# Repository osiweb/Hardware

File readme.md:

## Synopsis

Ohio Scientific was one of the early makers of home computers, from the mid 70's to the mid 80's.  It's user base was small back then, and now a small number of hobbyists still hold some affection for these machines.  OSI hobbyists tend to appreciate the large, sparsely populated boards, which were easy to understand and hack.

This project aims preserve the designs by archiving the boards as quality gerbers, so that almost any OSI system can be reproduced.  Some boards have been scanned and post-processed.  Others have been recreated by hand.  This is a community project and any contributions are welcome.

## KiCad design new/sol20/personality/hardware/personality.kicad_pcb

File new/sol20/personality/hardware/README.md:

# Sol-20 unversal peronality module

## Introduction

This is a "Universal" personality module for the SOL-20.  It's features include:

* Up to 16 ROM images, which can be selected by jumper configuration.

* Supports 27/28C256, 27/28C128, 27/28C64

* Supports remapping ROM, sysem RAM, and video to Fxxx, with a trivial mod to
  the motherboard (and re-assembling ROM images to run at F000). The mod does
  not require cutting any traces, so it's fully reversible and doesn't require
  modifications to other personality modules to be used with the modified
  mainboard, unlike the modification described in the Micro Complex manual.

## Parts

1. U1 - 74LS08

1. U2 - 27C256/28C256/27C128/28C128/27C64/28C64, or compatible parts.

1. RN1 - SIP resistor network with common pin 1. Any 6-, 7-, or 8 resistor
   network in the 3.3K-10K range will be fine, as long as you place it on the
   board with pin 1 in the right spot.

1. RN2 - SIP resistor network with common pin 1. Can use the same part as RN1.
   Any value in the 1K-20K range will work. Minimal current through this
   network. is fine, and you can use any value at all, or even just solder a
   wire across all the pins (negligible current should flow through the
   network).

1. JP1 - 2 x 8 pin 0.1" breakaway header.

## Fxxx mapping modification - no mainboard modification

1. You may want to order a spare DIP 74LS136 chip. This is the quad
   open-collector XOR gate at U22. Not only will this let you preserve the
   original chip with the correct date code; you will have to solder some wires directly
   to the pins of U22, and this might be easier and cleaner on a new chip rather than an
   old chip wiht oxidized leads.

1. Make or buy a 2-wire cable with 2-pin female socket header.  You can buy one premade,
   such as [this one from Sparkfun](https://www.sparkfun.com/products/10372.

1. With the universal personality module inserted, install the cable header on
   the PCB pin header position labeled "Map header". This is on the far right if
   the edge connector is facing you.
   
1. Neatly route the cable from the header to pins 3 and 5 of U22, leaving a bit
   of slack.
   
1. Cut the cable to length, and strip 2mm from the cable ends.

1. Solder the cable wires to pins 3 and 5 of of a 74LS136 chip. If you solder
   the wire with the chip removed from the main board, you can make a clean
   joint without worrying about damaging the socket or splashing solder on the
   main board.

1. Plug the 74LS136 in the U22 socket

1. Plug the female cable connector into the "Map Header" pins Route the cable
   neatly, securing it with small tie wraps where possible.
   
<!-- ## Fxxx mapping modification - No cable (Requires mainboard removal, which is somwhat involved) (NOT RECOMMENDED -- THIS IS NOT TESTED, AND NEEDS TO BE REVIEWED) -->

<!-- 1. Remove the SOL-PC mainboard from the case. -->
<!-- 1. Solder a jumper wire between pin 3 of U22 and pin B2 of J5 (the personality module connector.) -->
<!-- 1. Solder a jumper wire between pin 5 of U22 and pin B3 of J5. -->
<!-- 1. Reinstall the SOL-PC mainboard and reassemble. -->

## To remap the ROM, system RAM, and video to Fxxx (with one of the mods above)

1. First, make sure the selected ROM image is compiled for Fxxx.

1. Place a jumper in the "Map Fxxx" position.

1. To revert to Cxxx, make sure the selected image is compiled for Cxxx and
   remove the "Map Fxxx" jumper.

## Notes

1. For the SEL0-3 lines, a jumper pulls the line LOW, so the 000 block will
   require 3 jumpers. If you want a jumper to indicate a logical 1, then invert
   the ordering of the images in the (E)EPROM. I.E., place the first image at
   111, second at 110, third at 101, etc. Since that can all be handled in a
   script, that's not a bad way to go.

1. For a 'C128, leave Sel3 open. For a 'C64, leave Sel 2 and Sel 3 open.

1. If you use a 28C256 or 27C256, you need to jumper-select the (E)EPROM type.
   For a 27C256, place the jumper at the 27C256 position. For 28C256 place the
   jumper at 28C256 position.  For all other types, leave both jumpers empty.

1. The Resistor network values are not critical at all. The two networks don't
   need to be the same, or even have the same number of pins, as long as there
   are at least 6 resistors, and pin 1 is the common pin.

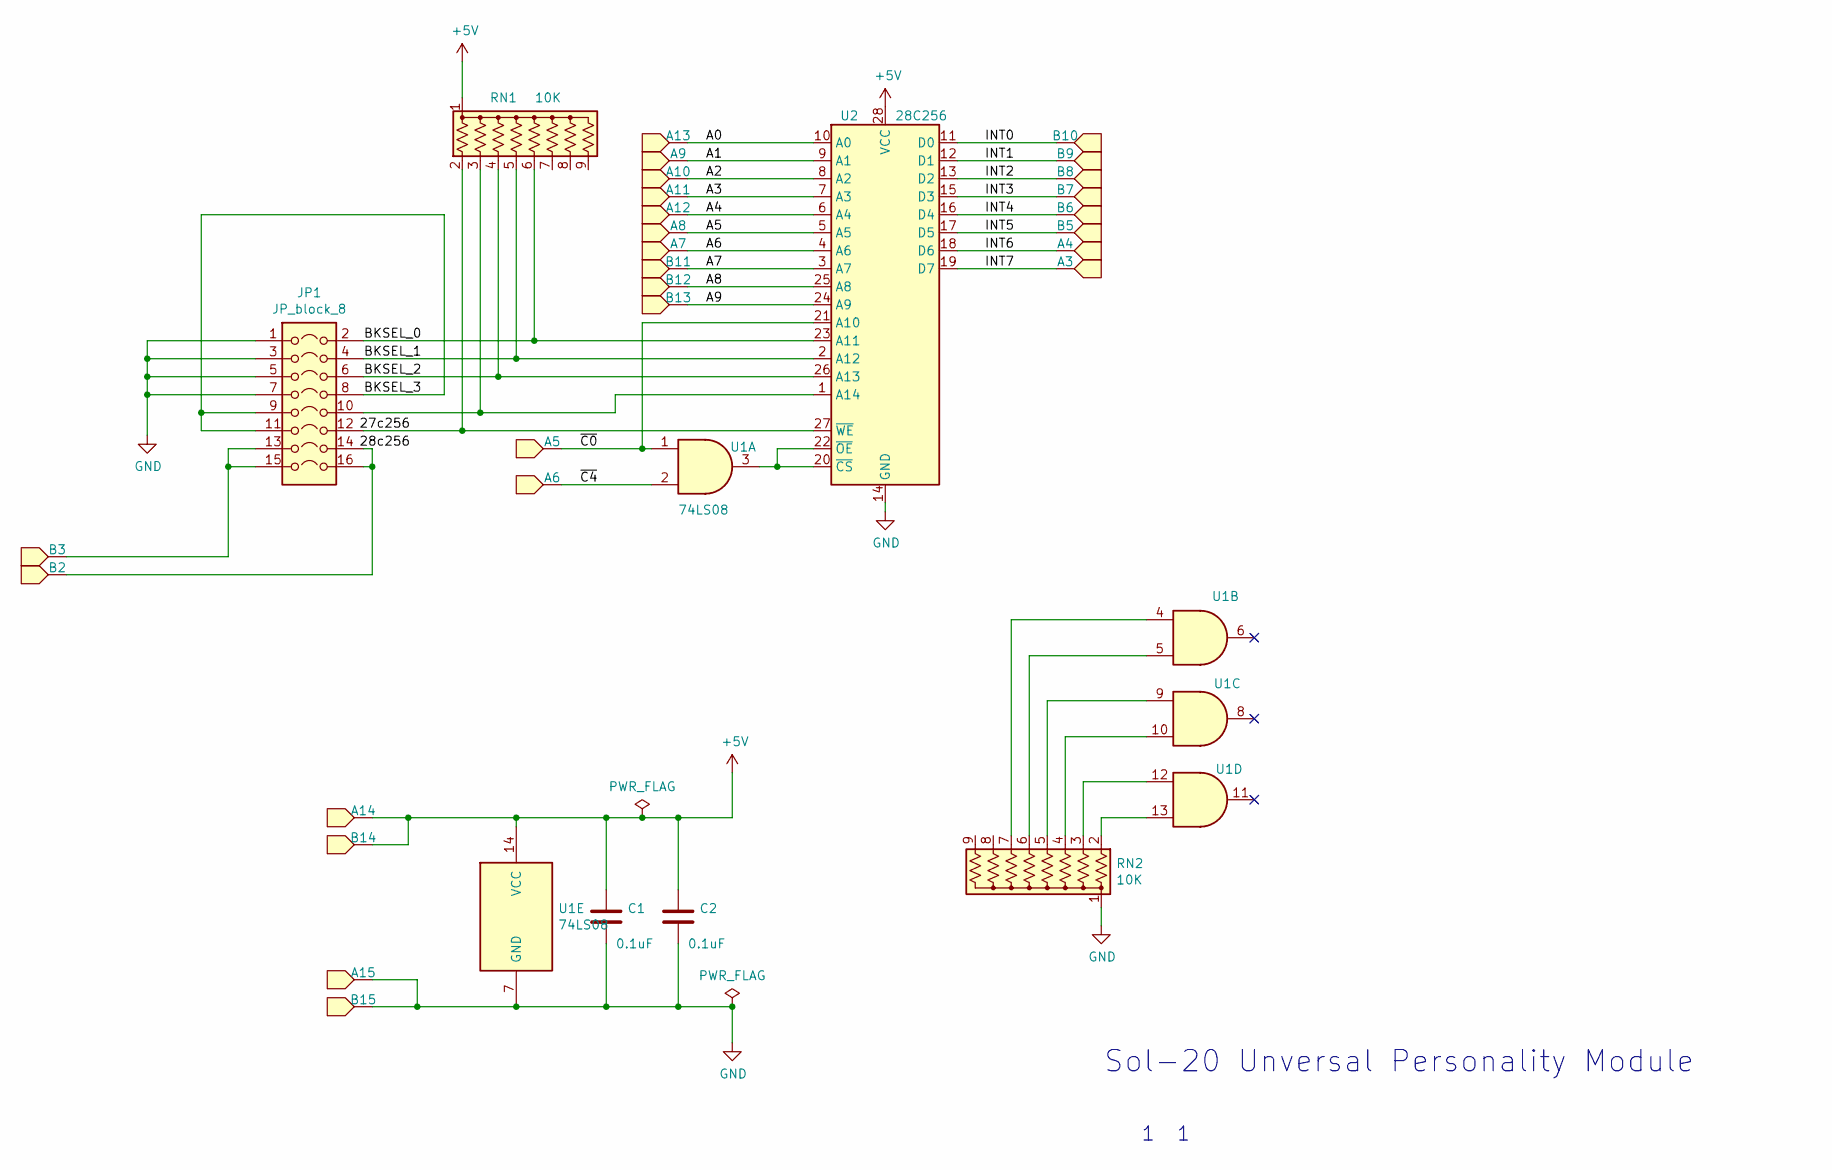
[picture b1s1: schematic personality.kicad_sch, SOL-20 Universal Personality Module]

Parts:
C1, C2: 0.1uF; C_Disc_D3.8mm_W2.6mm_P2.50mm
J1: Personality-connector; edge-sol-personaltiy-2.54-30
JP1: JP_block_8; PinHeader_2x08_P2.54mm_Vertical
RN1, RN2: 10K; R_Array_SIP9
U1: 74LS08; DIP-14_W7.62mm
U2: 28C256; DIP-28_W15.24mm

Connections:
+5V: C1.1, C2.1, J1.A14, J1.B14, RN1.1 (common), U1.14 (VCC), U2.28 (VCC)
/A0: J1.A13, U2.10 (A0)
/A1: J1.A9, U2.9 (A1)
/A2: J1.A10, U2.8 (A2)
/A3: J1.A11, U2.7 (A3)
/A4: J1.A12, U2.6 (A4)
/A5: J1.A8, U2.5 (A5)
/A6: J1.A7, U2.4 (A6)
/A7: J1.B11, U2.3 (A7)
/A8: J1.B12, U2.25 (A8)
/A9: J1.B13, U2.24 (A9)
/BKSEL_0: JP1.2, RN1.6 (R5), U2.23 (A11)
/BKSEL_1: JP1.4, RN1.5 (R4), U2.2 (A12)
/BKSEL_2: JP1.6, RN1.4 (R3), U2.26 (A13)
/BKSEL_3: JP1.8, JP1.9, JP1.11
/INT0: J1.B10, U2.11 (D0)
/INT1: J1.B9, U2.12 (D1)
/INT2: J1.B8, U2.13 (D2)
/INT3: J1.B7, U2.15 (D3)
/INT4: J1.B6, U2.16 (D4)
/INT5: J1.B5, U2.17 (D5)
/INT6: J1.A4, U2.18 (D6)
/INT7: J1.A3, U2.19 (D7)
/~C0: J1.A5, U1.1, U2.21 (A10)
/~C4: J1.A6, U1.2
GND: C1.2, C2.2, J1.A15, J1.B15, JP1.1, JP1.3, JP1.5, JP1.7, RN2.1 (common), U1.7 (GND), U2.14 (GND)
unnamed: J1.B2, JP1.14, JP1.16
unnamed: J1.B3, JP1.13, JP1.15
unnamed: JP1.10, RN1.3 (R2), U2.1 (A14)
unnamed: JP1.12, RN1.2 (R1), U2.27 (~WE)
unnamed: RN2.2 (R1), U1.13
unnamed: RN2.3 (R2), U1.12
unnamed: RN2.4 (R3), U1.10
unnamed: RN2.5 (R4), U1.9
unnamed: RN2.6 (R5), U1.5
unnamed: RN2.7 (R6), U1.4
unnamed: U1.3, U2.20 (~CS), U2.22 (~OE)

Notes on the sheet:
Sol-20 Unversal Personality Module
1 1

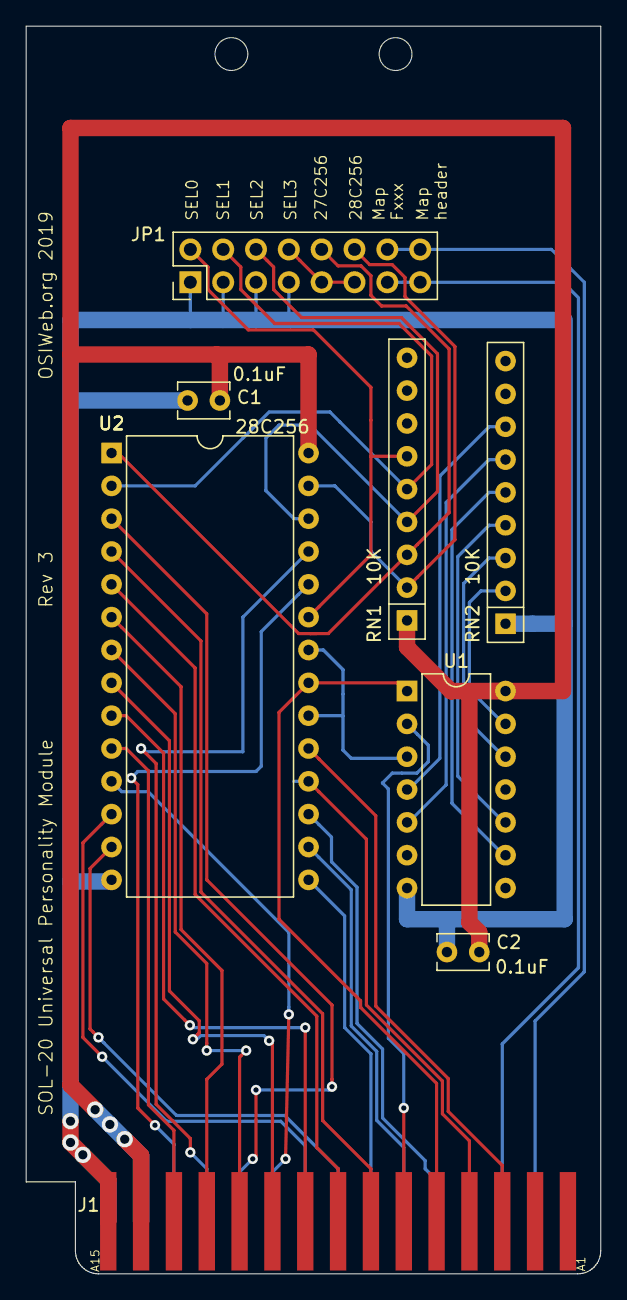
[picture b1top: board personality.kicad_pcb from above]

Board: 2 copper layers, 44.4 x 96.5 mm, 8 parts (0 on the bottom side), 37 nets.

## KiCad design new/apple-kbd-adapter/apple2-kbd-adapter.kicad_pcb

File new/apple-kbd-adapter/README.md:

# Apple 2 keyboard adapter for Apple 1 computer
This is a simple adapter to connect an Apple 2 compatible keyboard to an Apple 1
computer. The pinouts were obtained from the article [Using an Apple II Keyboard
with an Apple 1
Computer](http://randomvariations.com/2014/10/16/using-an-apple-ii-keyboard-with-an-apple-1-computer/)
at [Randomvariations.com](https://randomvariations.com).

There are similar adapter boards for sale through various sources. This design
based only on the referenced article. Any similarities to alternative adapters
is coincidental and due solely to the simplicity of the design, and obvious
requirements such as the desire for reset and clear buttons mounted on the board
and remotely.

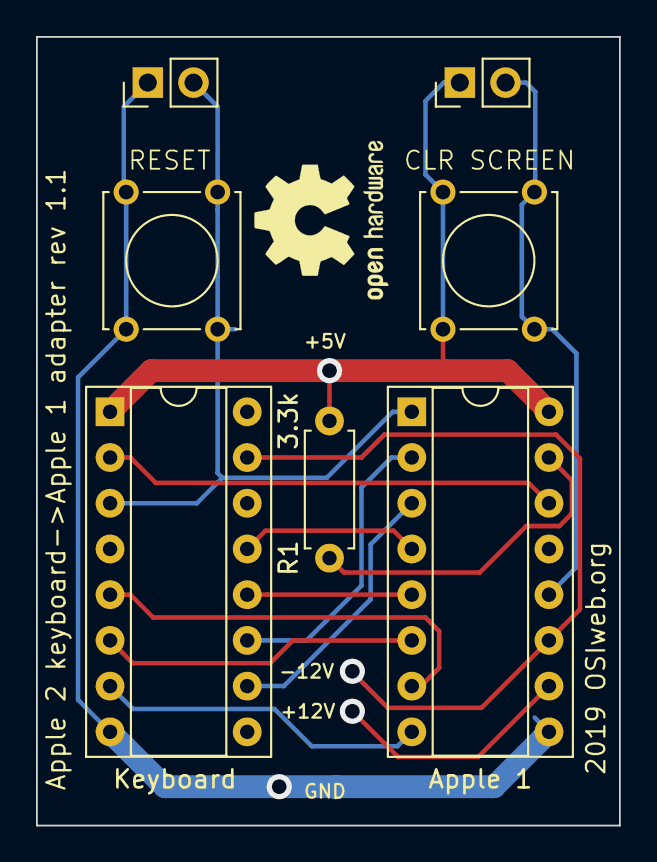
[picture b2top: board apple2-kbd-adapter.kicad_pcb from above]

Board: 2 copper layers, 32.4 x 43.8 mm, 7 parts (0 on the bottom side), 14 nets.

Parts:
J1: Apple 1; DIP-16_W7.62mm_Socket
J2: ~RESET; PinHeader_1x02_P2.54mm_Vertical
J3: ~CLEAR_SCREEN; PinHeader_1x02_P2.54mm_Vertical
J4: Keyboard; DIP-16_W7.62mm_Socket
R1: 3.3k; R_Axial_DIN0207_L6.3mm_D2.5mm_P7.62mm_Horizontal
SW1, SW2: SW_SPST; SW_Tactile_Straight_KSL0Axx1LFTR

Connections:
/+5V: J1.16, J3.1, J4.1, R1.2, SW2.1
/-12V: J1.11, J4.15
/D1: J1.5, J4.12
/D2: J1.4, J4.13
/D3: J1.3, J4.10
/D4: J1.2, J4.11
/D5: J1.6, J4.6
/D6: J1.7, J4.5
/D7: J1.8, J4.7
/D8: J1.15, R1.1
/GND: J1.9, J2.1, J4.8, SW1.1
/~CLRSCR: J1.12, J3.2, SW2.2
/~RESET: J1.1, J2.2, J4.3, SW1.2
/~STROBE: J1.14, J4.2

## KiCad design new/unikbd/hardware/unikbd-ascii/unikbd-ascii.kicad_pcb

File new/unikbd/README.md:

## Universal ASCII Keyboard

This project aims to provide a (near) universal ASCII keyboard for vintage computers.  Home computers of the 1970's typically either polled a switch matrix, or interfaced to a parallel ASCII keyboard via a parallel port.

The keyboard will allow use of Cherry MX keys, or the more period-correct George Risk KBM-01-01 (Futaba MD-4PCS) keys.

The keyboard supports diodes per-switch for true N-key rollover, or 
per-row (like the OSI).

The keyboard is designed using KiCad in order to be the most useful for anybody wishing to modify the keyboard for more specific uses, or to add to the project.

Goals for the keyboard:

- Drop in replacement for Ohio Scientific polled keyboards
-- Done: drop in interface module for OSI 542 (untested). 
-- Done: keycap set available
-- To do: module for advanced 542B/C features

- Drop in replacement for Apple II keyboard
--Done: Add-in ASCII interface module with Apple 1 and Apple 2 connectors
--To do: Special Apple keycaps needed for some keys: (Bel/G), (^/N), arrows, RESET.

- Standard ASCII parallel keyboard
-- Done: Keycap set available
-- Done: Add-in ASCII interface module.

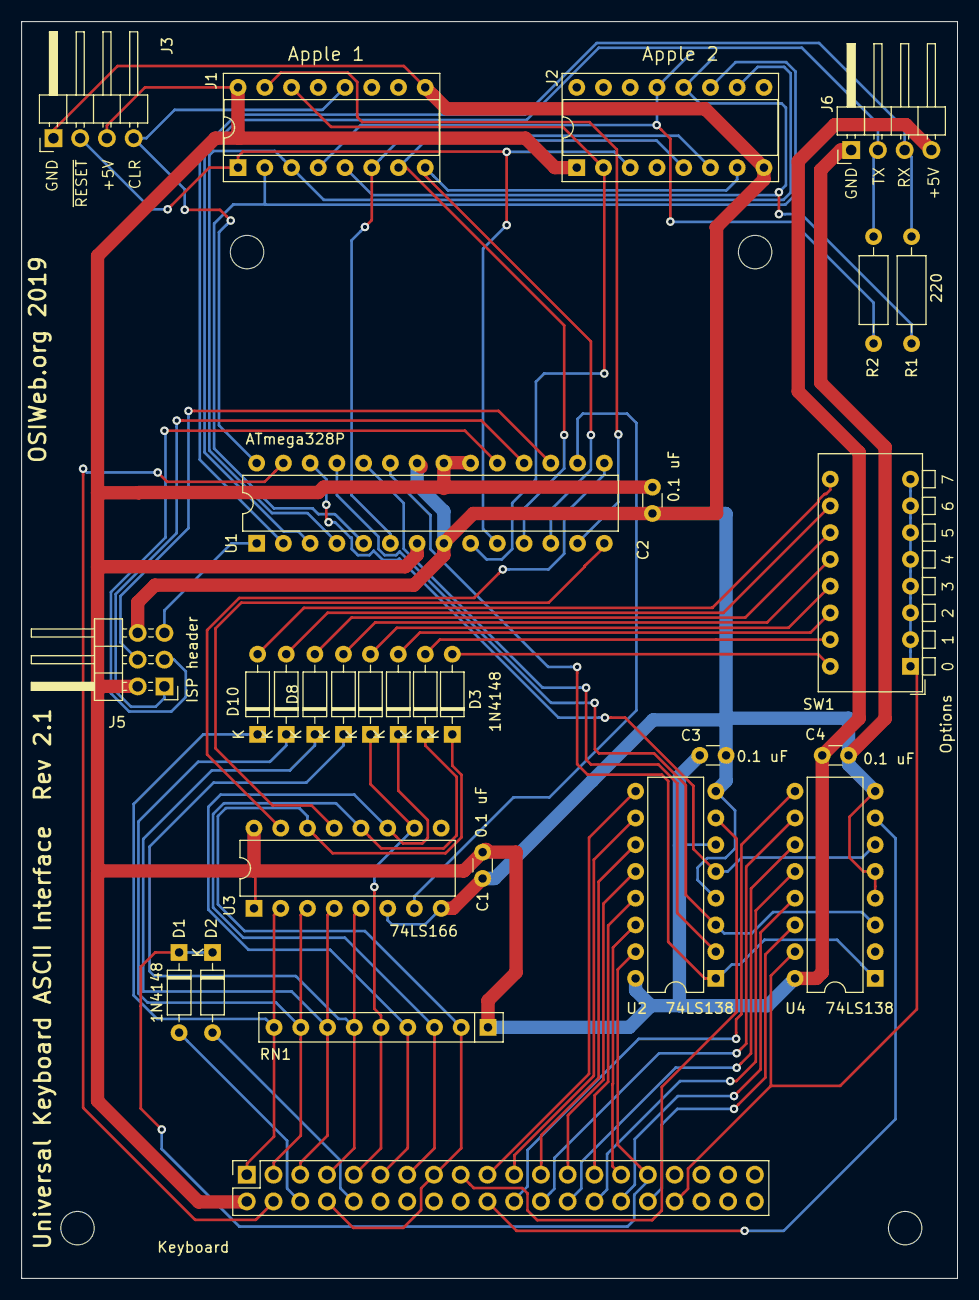
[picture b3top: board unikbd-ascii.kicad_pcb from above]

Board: 2 copper layers, 88.9 x 119.4 mm, 28 parts (0 on the bottom side), 61 nets.

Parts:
C1, C2, C3, C4: 0.1 uF; C_Disc_D3.0mm_W1.6mm_P2.50mm
D1, D2, D3, D4, D5, D6, D7, D8, D9, D10: 1N4148; D_DO-35_SOD27_P7.62mm_Horizontal
J1: Apple 1; DIP-16_W7.62mm_Socket
J2: Apple 2; DIP-16_W7.62mm_Socket
J3: Reset/Clr; PinHeader_1x04_P2.54mm_Horizontal
J4: Keyboard; PinHeader_2x20_P2.54mm_Vertical
J5: ISP header; PinHeader_2x03_P2.54mm_Horizontal
J6: UART; PinHeader_1x04_P2.54mm_Horizontal
R1: 220; R_Axial_DIN0207_L6.3mm_D2.5mm_P10.16mm_Horizontal
R2: R_US; R_Axial_DIN0207_L6.3mm_D2.5mm_P10.16mm_Horizontal
RN1: 4.7k; R_Array_SIP9
SW1: Options; SW_DIP_SPSTx08_Piano_CTS_Series194-8MSTN_W7.62mm_P2.54mm
U1: ATmega328P; DIP-28_W7.62mm
U2, U4: 74LS138; DIP-16_W7.62mm
U3: 74LS166; DIP-16_W7.62mm

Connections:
+5V: C1.1, C2.1, C3.1, C4.1, J1.16, J2.1, J3.3, J4.2, J5.2, J6.4, RN1.1, U1.7, U1.20, U1.21, U2.6, U2.16, U3.1, U3.16, U4.16
/CAPS_LED: J4.4, U1.27
/ClrScr: J1.12, J3.4, U1.28
/Col0: D3.1, J4.8, J4.15, RN1.2, U3.14
/Col1: D4.1, J4.13, RN1.3, U3.12
/Col2: D5.1, J4.11, RN1.4, U3.11
/Col3: D6.1, J4.9, RN1.5, U3.10
/Col4: D7.1, J4.7, RN1.6, U3.5
/Col5: D8.1, J4.5, RN1.7, U3.4
/Col6: D9.1, J4.3, RN1.8, U3.3
/Col7: D10.1, J4.1, RN1.9, U3.2
/D0: J1.5, J2.12, R1.1
/D1: J1.4, J2.13, R2.1
/D2: J1.3, J2.10, U1.4
/D3: J1.2, J2.11, U1.5
/D4: J1.6, J2.6, U1.6
/D5: J1.7, J2.5, U1.11
/D6: J1.8, J2.7, U1.12
/D7: J1.15, U1.13
/MISO: J5.1, U1.18
/MOSI: J5.4, U1.17
/Row0: D1.1, D2.1, J4.31, U2.15
/Row1: J4.29, U2.14
/Row2: J4.27, U2.13
/Row3: J4.25, U2.12
/Row4: J4.23, U2.11
/Row5: J4.21, U2.10
/Row6: J4.19, U2.9
/Row7: J4.17, U2.7
/Row8: J4.34, SW1.1, SW1.2, SW1.3, SW1.4, SW1.5, SW1.6, SW1.7, SW1.8, U4.15
/Row9: J4.32, U4.14
/Row10: J4.30, U4.13
/Row11: J4.28, U4.12
/Row12: J4.26, U4.11
/Row13: J4.24, U4.10
/Row14: J4.22, U4.9
/Row15: J4.20, U4.7
/Rx: J6.3, R1.2, U1.2
/SCK: J5.3, U1.19
/Tx: J6.2, R2.2, U1.3
/~RESET: J5.5, U1.1
/~STROBE: J1.14, J2.2, U1.9
/~SYS_RESET: J1.1, J2.3, J3.2, U1.10
GND: C1.2, C2.2, C3.2, C4.2, J1.9, J2.8, J3.1, J5.6, J6.1, U1.8, U1.22, U2.4, U2.8, U3.6, U3.8, U4.4, U4.5, U4.8
unnamed: D1.2, J4.6
unnamed: D2.2, J4.10
unnamed: D3.2, SW1.16
unnamed: D4.2, SW1.15
unnamed: D5.2, SW1.14
unnamed: D6.2, SW1.13
unnamed: D7.2, SW1.12
unnamed: D8.2, SW1.11
unnamed: D9.2, SW1.10
unnamed: D10.2, SW1.9
unnamed: U1.14, U3.13
unnamed: U1.15, U3.15
unnamed: U1.16, U3.7
unnamed: U1.23, U2.1, U4.1
unnamed: U1.24, U2.2
unnamed: U1.25, U2.3, U4.3
unnamed: U1.26, U2.5, U4.6

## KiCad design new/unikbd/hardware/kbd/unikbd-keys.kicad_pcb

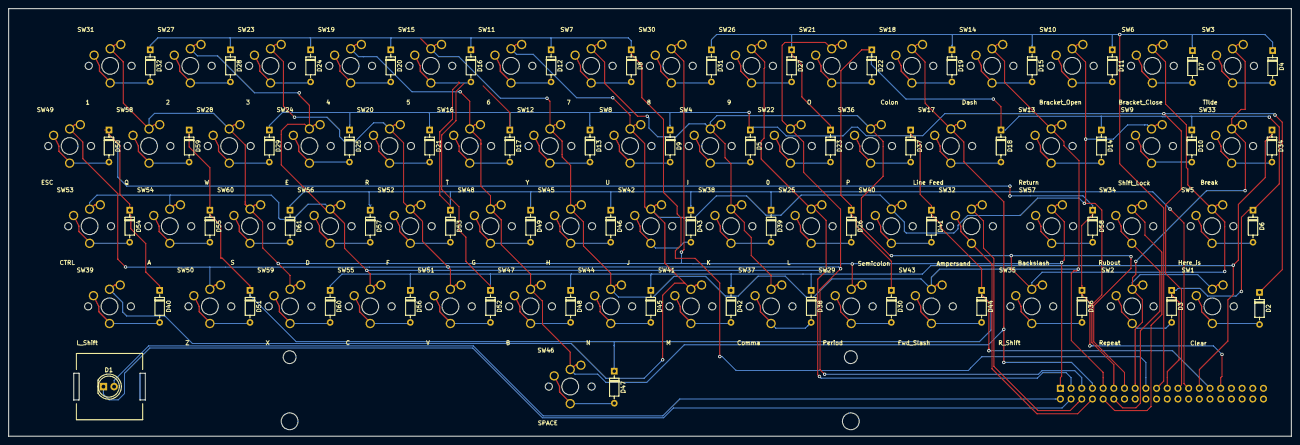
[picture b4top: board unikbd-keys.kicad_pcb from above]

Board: 2 copper layers, 304.8 x 101.6 mm, 120 parts (1 on the bottom side), 80 nets.

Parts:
D1: CQY99; LED_D5.0mm_IRGrey
D2, D3, D4, D5, D6, D7, D8, D9, D10, D11, D12, D13, D14, D15, D16, D17, D18, D19, D20, D21, D22, D23, D24, D25, D26, D27, D28, D29, D30, D31, D32, D34, D36, D37, D38, D39, D40, D41, D42, D43, D44, D45, D46, D47, D48, D49, D50, D51, D52, D53, D54, D55, D56, D57, D58, D59, D60, D61: 1N4148; D_DO-35_SOD27_P7.62mm_Horizontal
J1: Conn_02x20_Odd_Even; PinHeader_2x20_P2.54mm_Vertical
SW1: Clear; Key_MX
SW2: Repeat; Key_MX
SW3: Tilde; Key_MX
SW4: I; Key_MX
SW5: Here_is; Key_MX
SW6: Bracket_Close; Key_MX
SW7: 7; Key_MX
SW8: U; Key_MX
SW9: Shift_Lock; Key_MX
SW10: Bracket_Open; Key_MX
SW11: 6; Key_MX
SW12: Y; Key_MX
SW13: Return; Key_MX
SW14: Dash; Key_MX
SW15: 5; Key_MX
SW16: T; Key_MX
SW17: Line Feed; Key_MX
SW18: Colon; Key_MX
SW19: 4; Key_MX
SW20: R; Key_MX
SW21: O; Key_MX
SW22: 0; Key_MX
SW23: 3; Key_MX
SW24: E; Key_MX
SW25: L; Key_MX
SW26: 9; Key_MX
SW27: 2; Key_MX
SW28: W; Key_MX
SW29: Period; Key_MX
SW30: 8; Key_MX
SW31: 1; Key_MX
SW32: Ampersand; Key_MX
SW33: Break; Key_MX
SW34: Rubout; Key_MX
SW35: R_Shift; Key_MX
SW36: P; Key_MX
SW37: Comma; Key_MX
SW38: K; Key_MX
SW39: L_Shift; Key_MX
SW40: Semicolon; Key_MX
SW41: M; Key_MX
SW42: J; Key_MX
SW43: Fwd_Slash; Key_MX
SW44: N; Key_MX
SW45: H; Key_MX
SW46: SPACE; Key_MX
SW47: B; Key_MX
SW48: G; Key_MX
SW49: ESC; Key_MX
SW50: Z; Key_MX
SW51: V; Key_MX
SW52: F; Key_MX
SW53: CTRL; Key_MX
SW54: A; Key_MX
SW55: C; Key_MX
SW56: D; Key_MX
SW57: Backslash; Key_MX
SW58: Q; Key_MX
SW59: X; Key_MX
SW60: S; Key_MX

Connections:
/Col0: J1.15, SW1.1, SW2.1, SW3.1, SW33.1
/Col1: J1.13, SW4.1, SW5.1, SW6.1, SW7.1, SW35.1, SW36.1, SW37.1, SW38.1
/Col2: J1.11, SW8.1, SW9.1, SW10.1, SW11.1, SW39.1, SW40.1, SW41.1, SW42.1
/Col3: J1.9, SW12.1, SW13.1, SW14.1, SW15.1, SW43.1, SW44.1, SW45.1
/Col4: J1.7, SW16.1, SW17.1, SW18.1, SW19.1, SW46.1, SW47.1, SW48.1
/Col5: J1.5, SW20.1, SW21.1, SW22.1, SW23.1, SW49.1, SW50.1, SW51.1, SW52.1
/Col6: J1.3, SW24.1, SW25.1, SW26.1, SW27.1, SW53.1, SW54.1, SW55.1, SW56.1
/Col7: J1.1, SW28.1, SW29.1, SW30.1, SW31.1, SW57.1, SW58.1, SW59.1, SW60.1
/Row0: D36.1, D40.1, D50.1, D54.1, D58.1, J1.31
/Row1: D37.1, D41.1, D44.1, D47.1, D51.1, D55.1, D59.1, J1.29
/Row2: D34.1, D38.1, D42.1, D45.1, D48.1, D52.1, D56.1, D60.1, J1.27
/Row3: D39.1, D43.1, D46.1, D49.1, D53.1, D57.1, D61.1, J1.25
/Row4: D2.1, D5.1, D9.1, D13.1, D17.1, D21.1, D25.1, D29.1, J1.23
/Row5: D3.1, D6.1, D10.1, D14.1, D18.1, D22.1, D26.1, D30.1, J1.21
/Row6: D4.1, D7.1, D11.1, D15.1, D19.1, D23.1, D27.1, D31.1, J1.19
/Row7: D8.1, D12.1, D16.1, D20.1, D24.1, D28.1, D32.1, J1.17
unnamed: D1.1, J1.4
unnamed: D1.2, J1.2
unnamed: D2.2, SW1.2
unnamed: D3.2, SW2.2
unnamed: D4.2, SW3.2
unnamed: D5.2, SW4.2
unnamed: D6.2, SW5.2
unnamed: D7.2, SW6.2
unnamed: D8.2, SW7.2
unnamed: D9.2, SW8.2
unnamed: D10.2, SW9.2
unnamed: D11.2, SW10.2
unnamed: D12.2, SW11.2
unnamed: D13.2, SW12.2
unnamed: D14.2, SW13.2
unnamed: D15.2, SW14.2
unnamed: D16.2, SW15.2
unnamed: D17.2, SW16.2
unnamed: D18.2, SW17.2
unnamed: D19.2, SW18.2
unnamed: D20.2, SW19.2
unnamed: D21.2, SW20.2
unnamed: D22.2, SW21.2
unnamed: D23.2, SW22.2
unnamed: D24.2, SW23.2
unnamed: D25.2, SW24.2
unnamed: D26.2, SW25.2
unnamed: D27.2, SW26.2
unnamed: D28.2, SW27.2
unnamed: D29.2, SW28.2
unnamed: D30.2, SW29.2
unnamed: D31.2, SW30.2
unnamed: D32.2, SW31.2
unnamed: D34.2, SW33.2
unnamed: D36.2, SW35.2
unnamed: D37.2, SW36.2
unnamed: D38.2, SW37.2
unnamed: D39.2, SW38.2
unnamed: D40.2, SW39.2
unnamed: D41.2, SW40.2
unnamed: D42.2, SW41.2
unnamed: D43.2, SW42.2
unnamed: D44.2, SW43.2
unnamed: D45.2, SW44.2
unnamed: D46.2, SW45.2
unnamed: D47.2, SW46.2
unnamed: D48.2, SW47.2
unnamed: D49.2, SW48.2
unnamed: D50.2, SW49.2
unnamed: D51.2, SW50.2
unnamed: D52.2, SW51.2
unnamed: D53.2, SW52.2
unnamed: D54.2, SW53.2
unnamed: D55.2, SW54.2
unnamed: D56.2, SW55.2
unnamed: D57.2, SW56.2
unnamed: D58.2, SW57.2
unnamed: D59.2, SW58.2
unnamed: D60.2, SW59.2
unnamed: D61.2, SW60.2
unnamed: J1.6, SW32.1
unnamed: J1.8, SW32.2
unnamed: J1.10, SW34.1
unnamed: J1.12, SW34.2

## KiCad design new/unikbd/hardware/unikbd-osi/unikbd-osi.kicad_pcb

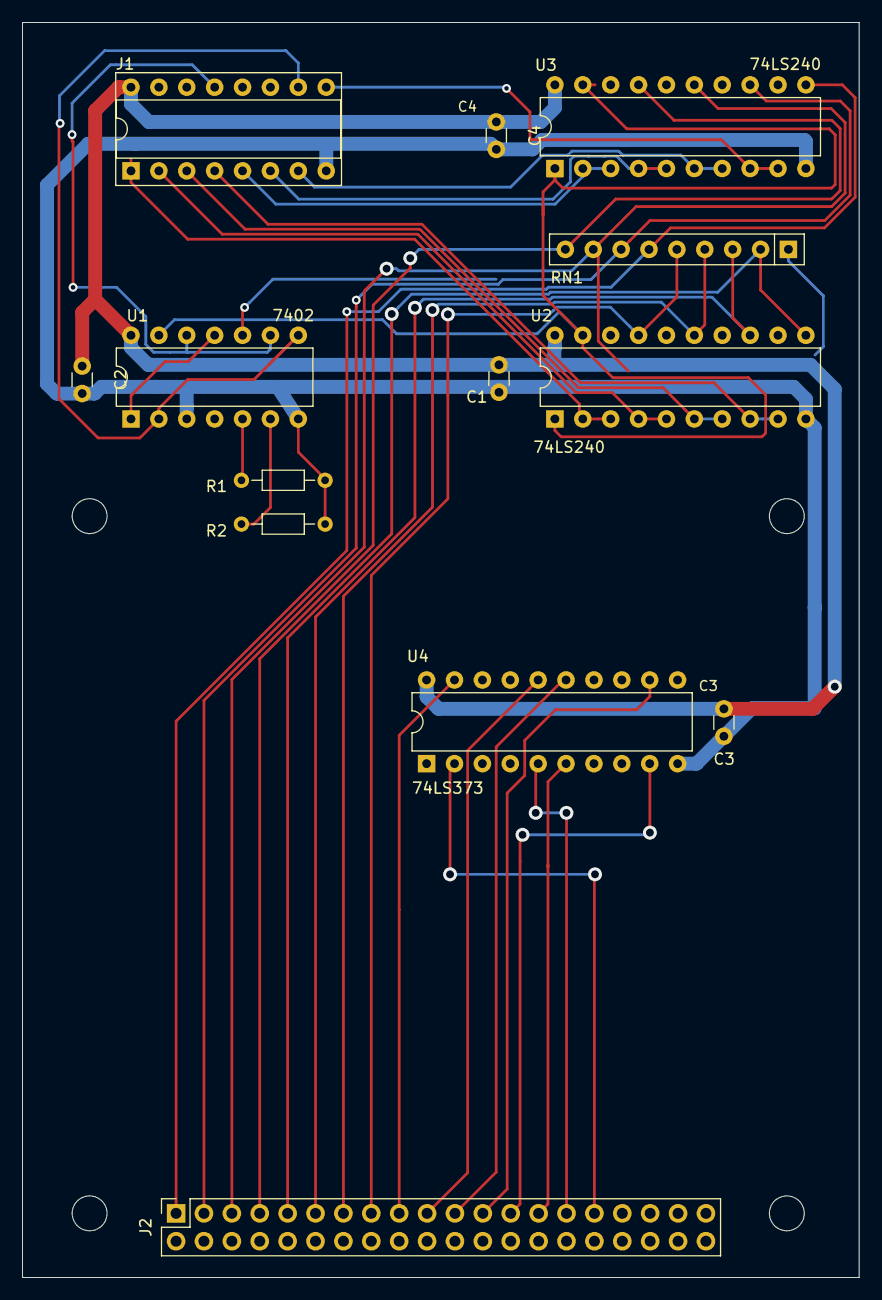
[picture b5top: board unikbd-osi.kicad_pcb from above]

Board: 2 copper layers, 76.2 x 114.3 mm, 13 parts (0 on the bottom side), 41 nets.

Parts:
C1, C2, C3: 0.1 uF; C_Disc_D3.0mm_W1.6mm_P2.50mm
C4: C; C_Disc_D3.0mm_W1.6mm_P2.50mm
J1: Conn_01x16; DIP-16_W7.62mm_Socket
J2: Conn_02x20_Odd_Even; PinSocket_2x20_P2.54mm_Vertical
R1, R2: 0 ohm; R_Axial_DIN0204_L3.6mm_D1.6mm_P7.62mm_Horizontal
RN1: 4.7k; R_Array_SIP9
U1: 7402; DIP-14_W7.62mm
U2, U3: 74LS240; DIP-20_W7.62mm
U4: 74LS373; DIP-20_W7.62mm

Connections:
+5V: C1.1, C2.1, C3.1, C4.1, J1.16, RN1.1, U1.14, U2.20, U3.20, U4.20
/Col0: J2.15, RN1.5, U2.17
/Col1: J2.13, RN1.4, U2.15
/Col2: J2.11, RN1.3, U2.13
/Col3: J2.9, RN1.2, U2.11
/Col4: J2.7, RN1.9, U3.17
/Col5: J2.5, RN1.8, U3.15
/Col6: J2.3, RN1.7, U3.13
/Col7: J2.1, RN1.6, U3.11
/D0: J1.1, U2.2, U2.3
/D1: J1.2, U2.4, U2.5
/D2: J1.3, U2.6, U2.7
/D3: J1.4, U2.8, U2.9
/D4: J1.5, U3.2, U3.3
/D5: J1.6, U3.4, U3.5
/D6: J1.7, U3.6, U3.7
/D7: J1.9, U3.8, U3.9
/R_~W: J1.10, U1.2, U1.8
/Row0: J2.31, U4.2
/Row1: J2.29, U4.5
/Row2: J2.27, U4.6
/Row3: J2.25, U4.9
/Row4: J2.23, U4.12
/Row5: J2.21, U4.15
/Row6: J2.19, U4.16
/Row7: J2.17, U4.19
/~KBE: J1.13, U1.9, U1.12
GND: C1.2, C2.2, C3.2, C4.2, J1.8, R1.2, R2.2, U1.3, U1.7, U2.10, U3.10, U4.1, U4.10
unnamed: R1.1, U1.5
unnamed: R2.1, U1.6
unnamed: U1.1, U1.11
unnamed: U1.10, U4.11
unnamed: U1.13, U2.1, U2.19, U3.1, U3.19
unnamed: U2.12, U4.8
unnamed: U2.14, U4.7
unnamed: U2.16, U4.4
unnamed: U2.18, U4.3
unnamed: U3.12, U4.18
unnamed: U3.14, U4.17
unnamed: U3.16, U4.14
unnamed: U3.18, U4.13

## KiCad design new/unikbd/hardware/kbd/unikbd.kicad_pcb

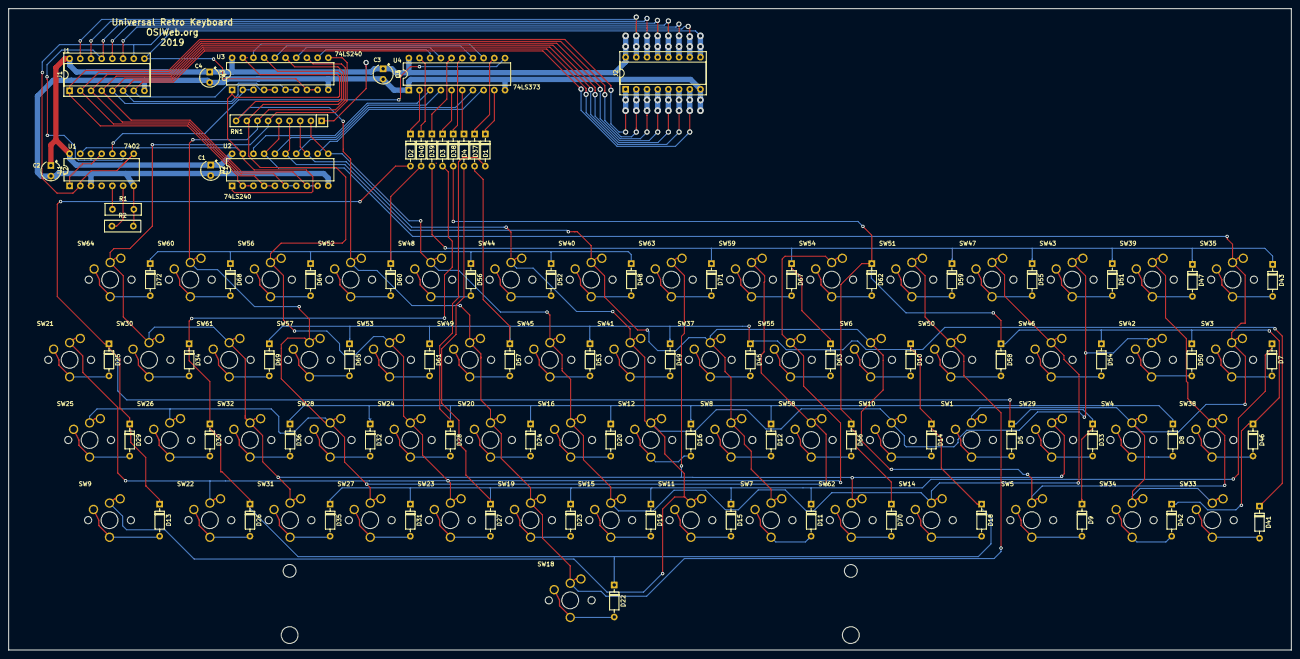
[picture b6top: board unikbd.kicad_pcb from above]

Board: 2 copper layers, 304.8 x 152.4 mm, 141 parts (0 on the bottom side), 113 nets.

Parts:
C1, C2, C3, C4: C; CP_Radial_Tantal_D4.5mm_P2.50mm
D1, D2, D3, D4, D5, D7, D8, D9, D10, D11, D12, D13, D14, D15, D16, D18, D19, D20, D22, D23, D24, D25, D26, D27, D28, D29, D30, D31, D32, D33, D34, D35, D36, D37, D38, D39, D40, D41, D42, D43, D45, D46, D47, D48, D49, D50, D51, D52, D53, D54, D55, D56, D57, D58, D59, D60, D61, D62, D63, D64, D65, D66, D67, D68, D69, D70, D71, D72: 1N4148; D_DO-35_SOD27_P7.62mm_Horizontal
J1, J2: Conn_01x16; DIP-16_W7.62mm_Socket
R1, R2: 0 ohm; R_Box_L8.4mm_W2.5mm_P5.08mm
RN1: 4.7k; R_Array_SIP9
SW1: Ampersand; Key_MX
SW3: Break; Key_MX
SW4: Rubout; Key_MX
SW5: R_Shift; Key_MX
SW6: P; Key_MX
SW7: Comma; Key_MX
SW8: K; Key_MX
SW9: L_Shift; Key_MX
SW10: Semicolon; Key_MX
SW11: M; Key_MX
SW12: J; Key_MX
SW14: Fwd_Slash; Key_MX
SW15: N; Key_MX
SW16: H; Key_MX
SW18: SPACE; Key_MX
SW19: B; Key_MX
SW20: G; Key_MX
SW21: ESC; Key_MX
SW22: Z; Key_MX
SW23: V; Key_MX
SW24: F; Key_MX
SW25: CTRL; Key_MX
SW26: A; Key_MX
SW27: C; Key_MX
SW28: D; Key_MX
SW29: Backslash; Key_MX
SW30: Q; Key_MX
SW31: X; Key_MX
SW32: S; Key_MX
SW33: Clear; Key_MX
SW34: Repeat; Key_MX
SW35: Tilde; Key_MX
SW37: I; Key_MX
SW38: Here_is; Key_MX
SW39: Bracket_Close; Key_MX
SW40: 7; Key_MX
SW41: U; Key_MX
SW42: Shift_Lock; Key_MX
SW43: Bracket_Open; Key_MX
SW44: 6; Key_MX
SW45: Y; Key_MX
SW46: Return; Key_MX
SW47: Dash; Key_MX
SW48: 5; Key_MX
SW49: T; Key_MX
SW50: Line Feed; Key_MX
SW51: Colon; Key_MX
SW52: 4; Key_MX
SW53: R; Key_MX
SW54: O; Key_MX
SW55: 0; Key_MX
SW56: 3; Key_MX
SW57: E; Key_MX
SW58: L; Key_MX
SW59: 9; Key_MX
SW60: 2; Key_MX
SW61: W; Key_MX
SW62: Period; Key_MX
SW63: 8; Key_MX
SW64: 1; Key_MX
U1: 7402; DIP-14_W7.62mm
U2, U3: 74LS240; DIP-20_W7.62mm
U4: 74LS373; DIP-20_W7.62mm

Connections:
+5V: C1.1, C2.1, C3.1, C4.1, J1.16, J2.16, RN1.1, U1.14, U2.20, U3.20, U4.20
/Col0: RN1.5, SW1.1, SW3.1, SW4.1, SW33.1, SW34.1, SW35.1, U2.17
/Col1: RN1.4, SW5.1, SW6.1, SW7.1, SW8.1, SW37.1, SW38.1, SW39.1, SW40.1, U2.15
/Col2: RN1.3, SW9.1, SW10.1, SW11.1, SW12.1, SW41.1, SW42.1, SW43.1, SW44.1, U2.13
/Col3: RN1.2, SW14.1, SW15.1, SW16.1, SW45.1, SW46.1, SW47.1, SW48.1, U2.11
/Col4: RN1.9, SW18.1, SW19.1, SW20.1, SW49.1, SW50.1, SW51.1, SW52.1, U3.17
/Col5: RN1.8, SW21.1, SW22.1, SW23.1, SW24.1, SW53.1, SW54.1, SW55.1, SW56.1, U3.15
/Col6: RN1.7, SW25.1, SW26.1, SW27.1, SW28.1, SW57.1, SW58.1, SW59.1, SW60.1, U3.13
/Col7: RN1.6, SW29.1, SW30.1, SW31.1, SW32.1, SW61.1, SW62.1, SW63.1, SW64.1, U3.11
/D0: J1.1, J2.1, U2.2, U2.3
/D1: J1.2, J2.2, U2.4, U2.5
/D2: J1.3, J2.3, U2.6, U2.7
/D3: J1.4, J2.4, U2.8, U2.9
/D4: J1.5, J2.5, U3.2, U3.3
/D5: J1.6, J2.6, U3.4, U3.5
/D6: J1.7, J2.7, U3.6, U3.7
/D7: J1.9, J2.9, U3.8, U3.9
/NI: J1.14, J2.14
/R_~W: J1.10, J2.10, U1.2, U1.8
/Row0: D2.1, U4.2
/Row1: D3.1, U4.5
/Row2: D4.1, U4.6
/Row3: D1.1, U4.9
/Row4: D37.1, U4.12
/Row5: D38.1, U4.15
/Row6: D39.1, U4.16
/Row7: D40.1, U4.19
/keys1/Row0_keys: D2.2, D5.1, D9.1, D13.1, D25.1, D29.1, D33.1
/keys1/Row1_keys: D3.2, D10.1, D14.1, D18.1, D22.1, D26.1, D30.1, D34.1
/keys1/Row2_keys: D4.2, D7.1, D11.1, D15.1, D19.1, D23.1, D27.1, D31.1, D35.1
/keys2/Row4_keys: D37.2, D41.1, D45.1, D49.1, D53.1, D57.1, D61.1, D65.1, D69.1
/keys2/Row5_keys: D38.2, D42.1, D46.1, D50.1, D54.1, D58.1, D62.1, D66.1, D70.1
/keys2/Row6_keys: D39.2, D43.1, D47.1, D51.1, D55.1, D59.1, D63.1, D67.1, D71.1
/keys2/Row7_keys: D40.2, D48.1, D52.1, D56.1, D60.1, D64.1, D68.1, D72.1
/~A0: J1.11, J2.11
/~A1: J1.12, J2.12
/~KBE: J1.13, J2.13, U1.9, U1.12
/~SI: J1.15, J2.15
GND: C1.2, C2.2, C3.2, C4.2, J1.8, J2.8, R1.2, R2.2, U1.3, U1.7, U2.10, U3.10, U4.1, U4.10
unnamed: D1.2, D8.1, D12.1, D16.1, D20.1, D24.1, D28.1, D32.1, D36.1
unnamed: D5.2, SW1.2
unnamed: D7.2, SW3.2
unnamed: D8.2, SW4.2
unnamed: D9.2, SW5.2
unnamed: D10.2, SW6.2
unnamed: D11.2, SW7.2
unnamed: D12.2, SW8.2
unnamed: D13.2, SW9.2
unnamed: D14.2, SW10.2
unnamed: D15.2, SW11.2
unnamed: D16.2, SW12.2
unnamed: D18.2, SW14.2
unnamed: D19.2, SW15.2
unnamed: D20.2, SW16.2
unnamed: D22.2, SW18.2
unnamed: D23.2, SW19.2
unnamed: D24.2, SW20.2
unnamed: D25.2, SW21.2
unnamed: D26.2, SW22.2
unnamed: D27.2, SW23.2
unnamed: D28.2, SW24.2
unnamed: D29.2, SW25.2
unnamed: D30.2, SW26.2
unnamed: D31.2, SW27.2
unnamed: D32.2, SW28.2
unnamed: D33.2, SW29.2
unnamed: D34.2, SW30.2
unnamed: D35.2, SW31.2
unnamed: D36.2, SW32.2
unnamed: D41.2, SW33.2
unnamed: D42.2, SW34.2
unnamed: D43.2, SW35.2
unnamed: D45.2, SW37.2
unnamed: D46.2, SW38.2
unnamed: D47.2, SW39.2
unnamed: D48.2, SW40.2
unnamed: D49.2, SW41.2
unnamed: D50.2, SW42.2
unnamed: D51.2, SW43.2
unnamed: D52.2, SW44.2
unnamed: D53.2, SW45.2
unnamed: D54.2, SW46.2
unnamed: D55.2, SW47.2
unnamed: D56.2, SW48.2
unnamed: D57.2, SW49.2
unnamed: D58.2, SW50.2
unnamed: D59.2, SW51.2
unnamed: D60.2, SW52.2
unnamed: D61.2, SW53.2
unnamed: D62.2, SW54.2
unnamed: D63.2, SW55.2
unnamed: D64.2, SW56.2
unnamed: D65.2, SW57.2
unnamed: D66.2, SW58.2
unnamed: D67.2, SW59.2
unnamed: D68.2, SW60.2
unnamed: D69.2, SW61.2
unnamed: D70.2, SW62.2
unnamed: D71.2, SW63.2
unnamed: D72.2, SW64.2
unnamed: R1.1, U1.5
unnamed: R2.1, U1.6
unnamed: U1.1, U1.11
unnamed: U1.10, U4.11
unnamed: U1.13, U2.1, U2.19, U3.1, U3.19
unnamed: U2.12, U4.8
unnamed: U2.14, U4.7
unnamed: U2.16, U4.4
unnamed: U2.18, U4.3
unnamed: U3.12, U4.18
unnamed: U3.14, U4.17
unnamed: U3.16, U4.14
unnamed: U3.18, U4.13

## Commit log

2017-04-02 add in production packages
2017-04-02 added A15 docs to package doc directory
2017-04-02 updated A15 zip to include manual
2017-04-10 Create reproductions folder
2017-04-10 added scan zip files
2017-04-10 add new projects directory
2017-04-10 add reproduction projects directory
2017-04-10 move reproduction fils to repro directory
2017-04-10 added Klyball 600D and 610 reproduction gerbers
2017-04-10 rename 600 and 610 files for consistency
2018-07-01 Fixed ABOUT header
2018-07-01 minor fixes
2018-09-26 updated file permissions
2018-09-26 add OSI 542 polled keyboard
2019-06-25 initial keyboard commit
2019-06-25 add unikbd library to library table
2019-06-25 Add README file
2019-06-25 updated connector J1 footprint to socket
2019-06-25 update README file
2019-06-30 OSI 542 clone with 16-pin header extension
2019-07-20 Add unikbd-osi as separate directory
2019-07-20 Break out key matrix on smaller PCB, and have all decode and interface on daughter board.
2019-07-30 add Apple 2->Apple 1 keyboard adapter
2019-08-06 - fixed mislabeled keyboard and apple connectors - swapped position of keyboard and apple connectors to be able to use same-side cables
2019-08-20 added sol-20 27c256/28c256 personality module
2019-09-06 update 502 files to fix missing traces
2019-09-06 Added Jeff Ferguson's assembly notes
2019-09-25 - Replaced DIP switch with 0.1" 8x2 header. Cheaper, smaller, more reliable - Replaced discrete resistors with resistor networks - Added jumper to select between 27C256 EPROMs and all other allowed E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
2019-09-25 use pins 1-7 on RN1, so shorter 6 and 7 resistor networks can be used in place.
2019-09-25 moved 5V rail from under silk screen
2019-09-25 add instructions for Fxxx remapping hardware mods.
2019-10-02 - fixed silk screen error (wrong string for RN2 value) - removed unnecessary pullup on the SEL3 jumper - renamed ~27C256 jumper to 27C256
2019-10-02 updated Readme.md to explain jumper settings for 27C256 and 28C256.
2019-10-07 - created hardware and roms subdirectories in personality project - added Personality Module assembler sources for several versions, lifted from sol20.org and deramp.com. Added Makefile to create 8K,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
2019-10-07 moved readme file to markup extension
2019-10-09 Fix assembler sources to work with A85
    - bootload.asm, consol.asm, solos*.asm: Change 'DW' to 'DB' to define command strings, because A85 treats
    the string as a 16-bit value and swaps the bytes to store as little-endian.
    - reassembled all the ROM images with the source DW->DB fix applied
    - modified README.md to explain the changes.
2019-10-09 Modify source files to work with A85
    - consol.asm, solos*.asm, cuter.asm: Define command strings with "DB" instead of
    "DW". DW treats the strings as 16-bit values, and swaps the bytes to store
    little-endian. DB stores in left-to-right order.
    - rebuild ROM images from fixed assembly sources.
2019-10-13 Add crv and dxf files for sol sides
2019-10-13 Add README file for Sol sides
2019-10-13 move sol side design files to proper directory
2019-10-14 Add test photo
2019-10-14 Add more pictures
2019-10-14 Add comparison photo and update README
2019-11-25 updates to keyboard alignment and ascii decoder
2019-12-10 * added DIP switches for controlling options (and diodes, since they are part of the matrix.
    * replaced 74154 with a pair of more readily available 74LS138's
    * fixed off-by-one error on keyboard connector.
    * added serial I/O, for bootloader, serial output option, debugging.
2020-01-14 Changed "melamine" to "masonite"
2020-03-03 Fixed CLEAR miswiring
    - (FIXED) The CLEAR button was wired to GROUND instead of +5V.
    - Added rev number to PCB and added design info to design sheets
    - Added no-connect symobols to unconnected pins on schematic
    - Added a README file.
2020-06-06 Removed unikbd from project list.
    The updated version has its own repository at:
    https://github.com/osiweb/unified_retro_keyboard
2020-07-04 Update kicad PCB file from nightly build to latest release.
2020-07-04 Add assembly rendering
2020-12-06 added Jeff Ferguson's build log and build guide
2020-12-06 Add README file to 502 directory
2020-12-06 Update README.org
    Added descriptions of each subdirectory
2020-12-06 Add parts list and errata for Klyball 542C
2020-12-06 Add README and Jeff Ferguson's build info for 540B board
2020-12-06 Update README.org
    convert long run-on headings into headings and descriptive paragraphs
2020-12-06 Add Jeff Ferguson's parts list.
2020-12-31 Readme updates Sol-20 Personality module
    - deprecate untested, unreviewed mainboard modification
    - add clarification for RN2
2021-12-06 Add PDF to visualize cutout plans
2022-10-07 Convert README from markdown to restructured text
    Also, add list of ROM contents for hex files.
2022-10-07 Fix tables in README
2022-10-07 Update instructions for rom remapping
2022-10-07 Clarify no mainboard mods for remapping.
2022-10-11 Board outline cleanup
    - round the corners of the edge connector
    - consolidate outline into polygon.
2022-10-15 Update to kicad v6
2026-06-21 include original SUperboard/600D
    - rename updated superboard to indicate that modification for cherry keys + EPROM
